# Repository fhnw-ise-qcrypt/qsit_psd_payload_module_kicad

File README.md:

# qsit_psd_payload_module_kicad
kicad drawings to interface a position sensitive detector (diode) for the QSIT payload

### BOM

https://octopart.com/bom-tool/2UpAKjyw

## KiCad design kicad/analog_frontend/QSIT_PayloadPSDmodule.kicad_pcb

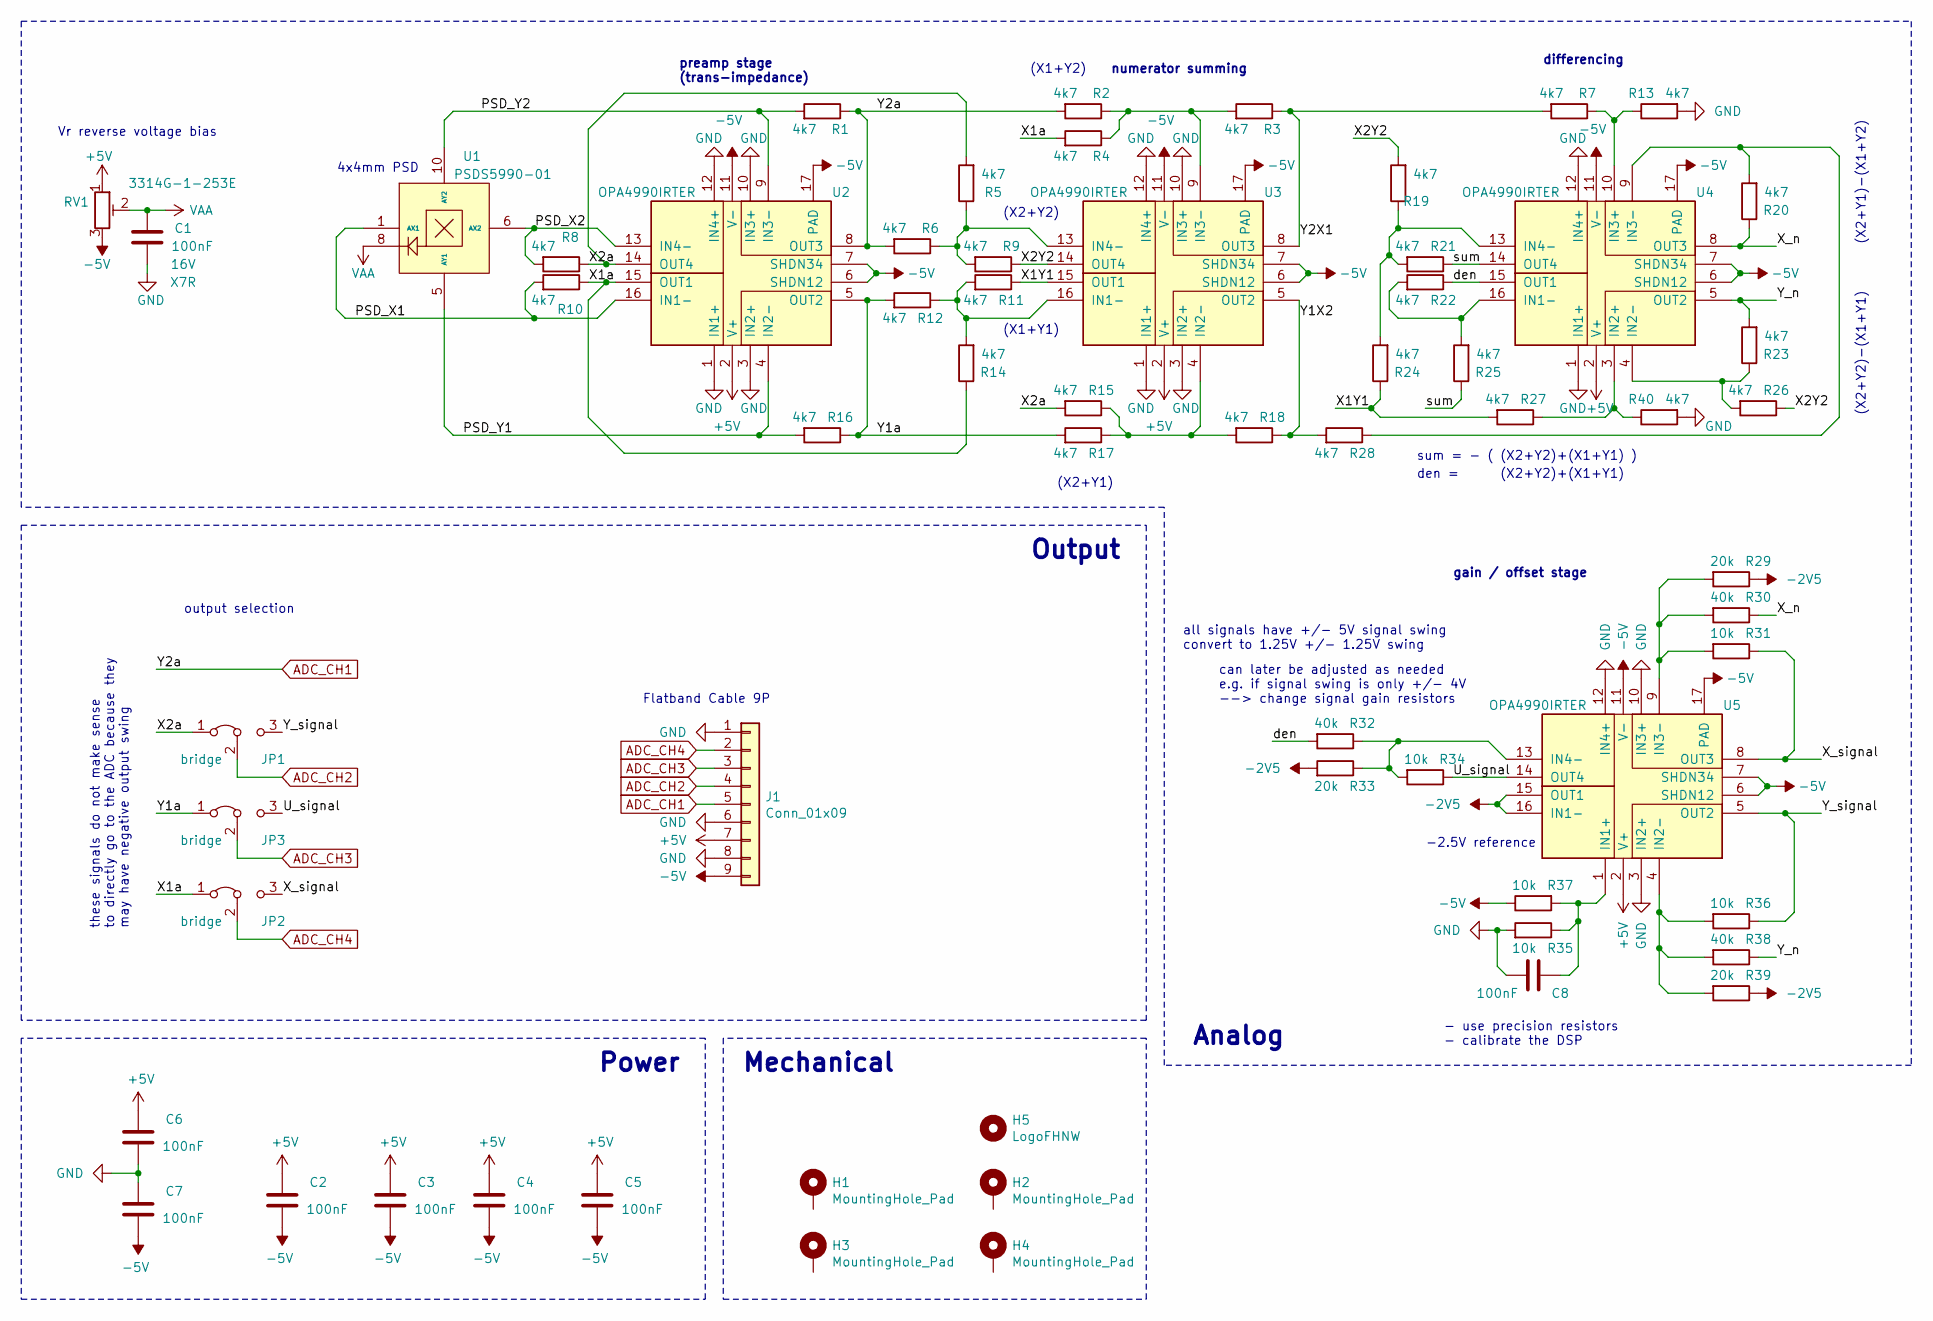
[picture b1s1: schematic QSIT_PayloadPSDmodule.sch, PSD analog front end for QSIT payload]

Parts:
C1: 100nF; C_0603_1608Metric_Pad1.08x0.95mm_HandSolder; Voltage 16V
C2, C3, C4, C5, C6, C7, C8: 100nF; C_0603_1608Metric_Pad1.08x0.95mm_HandSolder
H1, H2, H3, H4: MountingHole_Pad; MountingHole_2.5mm
H5: LogoFHNW; Logo_FHNW_03x05mm
J1: Conn_01x09; PinHeader_1x09_P2.54mm_Vertical
JP1, JP2, JP3: bridge; SolderJumper-3_P1.3mm_Open_RoundedPad1.0x1.5mm
R1, R2, R3, R4, R5, R6, R7, R8, R9, R10, R11, R12, R13, R14, R15, R16, R17, R18, R19, R20, R21, R22, R23, R24, R25, R26, R27, R28, R40: 4k7; R_0603_1608Metric_Pad0.98x0.95mm_HandSolder
R29, R33, R39: 20k; R_0603_1608Metric_Pad0.98x0.95mm_HandSolder
R30, R32, R38: 40k; R_0603_1608Metric_Pad0.98x0.95mm_HandSolder
R31, R34, R35, R36, R37: 10k; R_0603_1608Metric_Pad0.98x0.95mm_HandSolder
RV1: 3314G-1-253E; Potentiometer_Bourns_3314R-GM5_Vertical
U1: PSDS5990-01; HAMAMATSU_PSD_S599001_4mm
U2, U3, U4, U5: OPA4990IRTER; WQFN-16-1EP_3x3mm_P0.5mm_EP1.6x1.6mm

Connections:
+5V: C2.2, C3.2, C4.2, C5.2, C6.2, J1.7, RV1.1, U2.2 (V+), U3.2 (V+), U4.2 (V+), U5.2 (V+)
-2V5: R29.1, R33.2, R39.1, U5.15 (OUT1), U5.16 (IN1-)
-5V: C2.1, C3.1, C4.1, C5.1, C7.1, J1.9, R37.1, RV1.3, U2.6 (SHDN12), U2.7 (SHDN34), U2.11 (V-), U2.17 (PAD), U3.6 (SHDN12), U3.7 (SHDN34), U3.11 (V-), U3.17 (PAD), U4.6 (SHDN12), U4.7 (SHDN34), U4.11 (V-), U4.17 (PAD), U5.6 (SHDN12), U5.7 (SHDN34), U5.11 (V-), U5.17 (PAD)
/PSD_X1: R10.2, U1.1 (AX1), U2.16 (IN1-)
/PSD_X2: R8.2, U1.6 (AX2), U2.13 (IN4-)
/PSD_Y1: R16.2, U1.5 (AY1), U2.4 (‌IN2-)
/PSD_Y2: R1.2, U1.10 (AY2), U2.9 (IN3-)
/U_signal: JP3.3 (B), R34.1, U5.14 (OUT4)
/X1Y1: R11.1, R24.1, R27.2, U3.15 (OUT1)
/X1a: JP2.1 (A), R4.2, R10.1, R14.1, U2.15 (OUT1)
/X2Y2: R9.1, R19.2, R26.1, U3.14 (OUT4)
/X2a: JP1.1 (A), R5.2, R8.1, R15.2, U2.14 (OUT4)
/X_n: R20.1, R30.1, U4.8 (OUT3)
/X_signal: JP2.3 (B), R31.1, U5.8 (OUT3)
/Y1X2: R18.1, R28.2, U3.5 (OUT2)
/Y1a: JP3.1 (A), R12.2, R16.1, R17.2, U2.5 (OUT2)
/Y2X1: R3.1, R7.2, U3.8 (OUT3)
/Y_n: R23.2, R38.1, U4.5 (OUT2)
/Y_signal: JP1.3 (B), R36.1, U5.5 (OUT2)
/den: R22.1, R32.2, U4.15 (OUT1)
/sum: R21.1, R25.1, U4.14 (OUT4)
ADC_CH1: J1.5, R1.1, R2.2, R6.2, U2.8 (OUT3)
ADC_CH2: J1.4, JP1.2 (C)
ADC_CH3: J1.3, JP3.2 (C)
ADC_CH4: J1.2, JP2.2 (C)
GND: C1.1, C6.1, C7.2, C8.1, J1.1, J1.6, J1.8, R13.2, R35.2, R40.2, U2.1 (IN1+), U2.3 (IN2+), U2.10 (IN3+), U2.12 (IN4+), U3.1 (IN1+), U3.3 (IN2+), U3.10 (IN3+), U3.12 (IN4+), U4.1 (IN1+), U4.12 (IN4+), U5.3 (IN2+), U5.10 (IN3+), U5.12 (IN4+)
unnamed: C8.2, R35.1, R37.2, U5.1 (IN1+)
unnamed: R2.1, R3.2, R4.1, U3.9 (IN3-)
unnamed: R5.1, R6.1, R9.2, U3.13 (IN4-)
unnamed: R11.2, R12.1, R14.2, U3.16 (IN1-)
unnamed: R7.1, R13.1, U4.10 (IN3+)
unnamed: R15.1, R17.1, R18.2, U3.4 (‌IN2-)
unnamed: R19.1, R21.2, R24.2, U4.13 (IN4-)
unnamed: R20.2, R28.1, U4.9 (IN3-)
unnamed: R22.2, R25.2, U4.16 (IN1-)
unnamed: R23.1, R26.2, U4.4 (‌IN2-)
unnamed: R27.1, R40.1, U4.3 (IN2+)
unnamed: R29.2, R30.2, R31.2, U5.9 (IN3-)
unnamed: R32.1, R33.1, R34.2, U5.13 (IN4-)
unnamed: R36.2, R38.2, R39.2, U5.4 (‌IN2-)
VAA: C1.2, RV1.2, U1.8

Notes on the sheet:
Vr reverse voltage bias
4x4mm PSD
preamp stage (trans-impedance)
numerator summing
differencing
(X2+Y1)
(X1+Y2)
(X1+Y1)
(X2+Y2)
(X2+Y1)-(X1+Y2)
(X2+Y2)-(X1+Y1)
den = (X2+Y2)+(X1+Y1)
sum = - ( (X2+Y2)+(X1+Y1) )
gain / offset stage
all signals have +/- 5V signal swing convert to 1.25V +/- 1.25V swing
can later be adjusted as needed e.g. if signal swing is only +/- 4V --> change signal gain resistors
Flatband Cable 9P
Mechanical
-2.5V reference
Power
Output
Analog
output selection
these signals do not make sense to directly go to the ADC because they may have negative output swing
- use precision resistors - calibrate the DSP

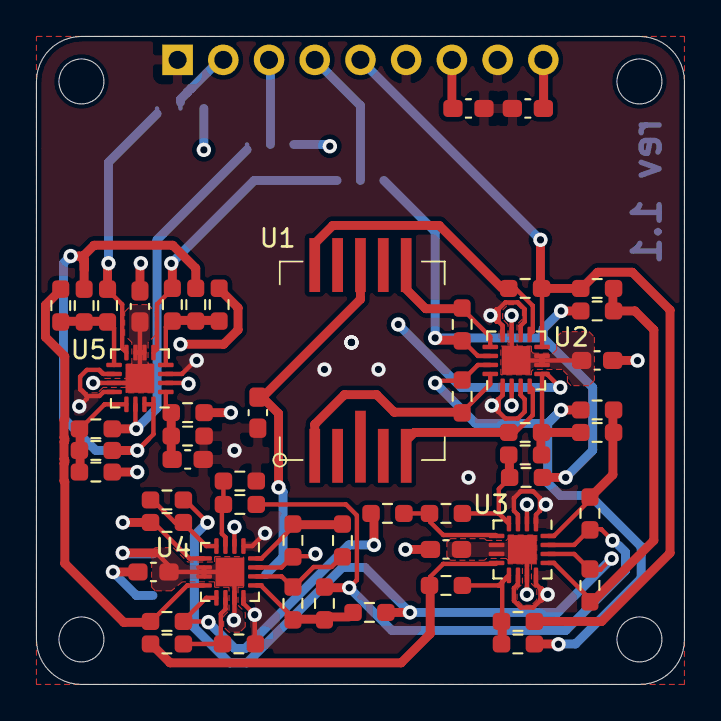
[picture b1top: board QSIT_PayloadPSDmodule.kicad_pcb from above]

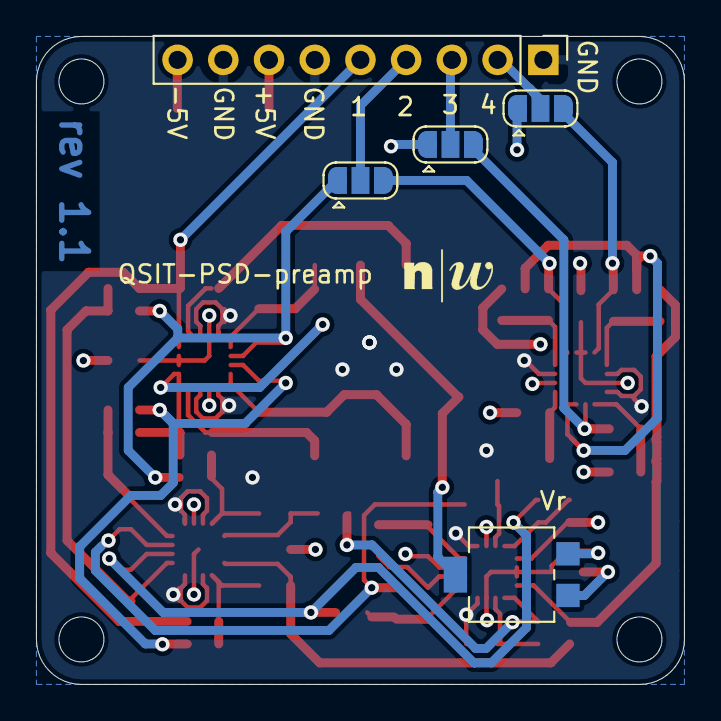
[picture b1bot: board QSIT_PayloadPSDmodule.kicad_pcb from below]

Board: 4 copper layers, 36.0 x 36.0 mm, 63 parts (6 on the bottom side), 41 nets.

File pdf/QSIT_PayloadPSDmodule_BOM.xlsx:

Reference | Quantity | Value | Footprint | Datasheet | Type | Voltage
C1 C2 C3 C4 C5 C6 C7 C8 | 8 | 100nF | Capacitor_SMD:C_0603_1608Metric_Pad1.08x0.95mm_HandSolder | ~ | X7R | 16V
H1 H2 H3 H4 | 4 | MountingHole_Pad | Mounting_Holes:MountingHole_2.5mm | ~
J1 | 1 | Conn_01x09 | Connector_PinHeader_2.54mm:PinHeader_1x09_P2.54mm_Vertical | ~
JP1 JP2 JP3 | 3 | bridge | Jumper:SolderJumper-3_P1.3mm_Open_RoundedPad1.0x1.5mm | ~
R1 R2 R3 R4 R5 R6 R7 R8 R9 R10 R11 R12 R13 R14 R15 R16 R17 R18 R19 R20 R21 R22 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 | 29 | 4k7 | Resistor_SMD:R_0603_1608Metric_Pad0.98x0.95mm_HandSolder | ~
R30 R32 R38 | 3 | 20k | Resistor_SMD:R_0603_1608Metric_Pad0.98x0.95mm_HandSolder | ~
R29 R31 R33 R34 R35 R36 R37 R39 | 8 | 10k | Resistor_SMD:R_0603_1608Metric_Pad0.98x0.95mm_HandSolder | ~
RV1 | 1 | 3314G-1-253E | Potentiometer_SMD:Potentiometer_Bourns_3314R-GM5_Vertical | ~
U1 | 1 | PSDS5990-01 | simonmartin_kicad_lib:HAMAMATSU_PSD_S599001_4mm
U2 U3 U4 U5 | 4 | OPA4990IRTER | Package_DFN_QFN:WQFN-16-1EP_3x3mm_P0.5mm_EP1.6x1.6mm

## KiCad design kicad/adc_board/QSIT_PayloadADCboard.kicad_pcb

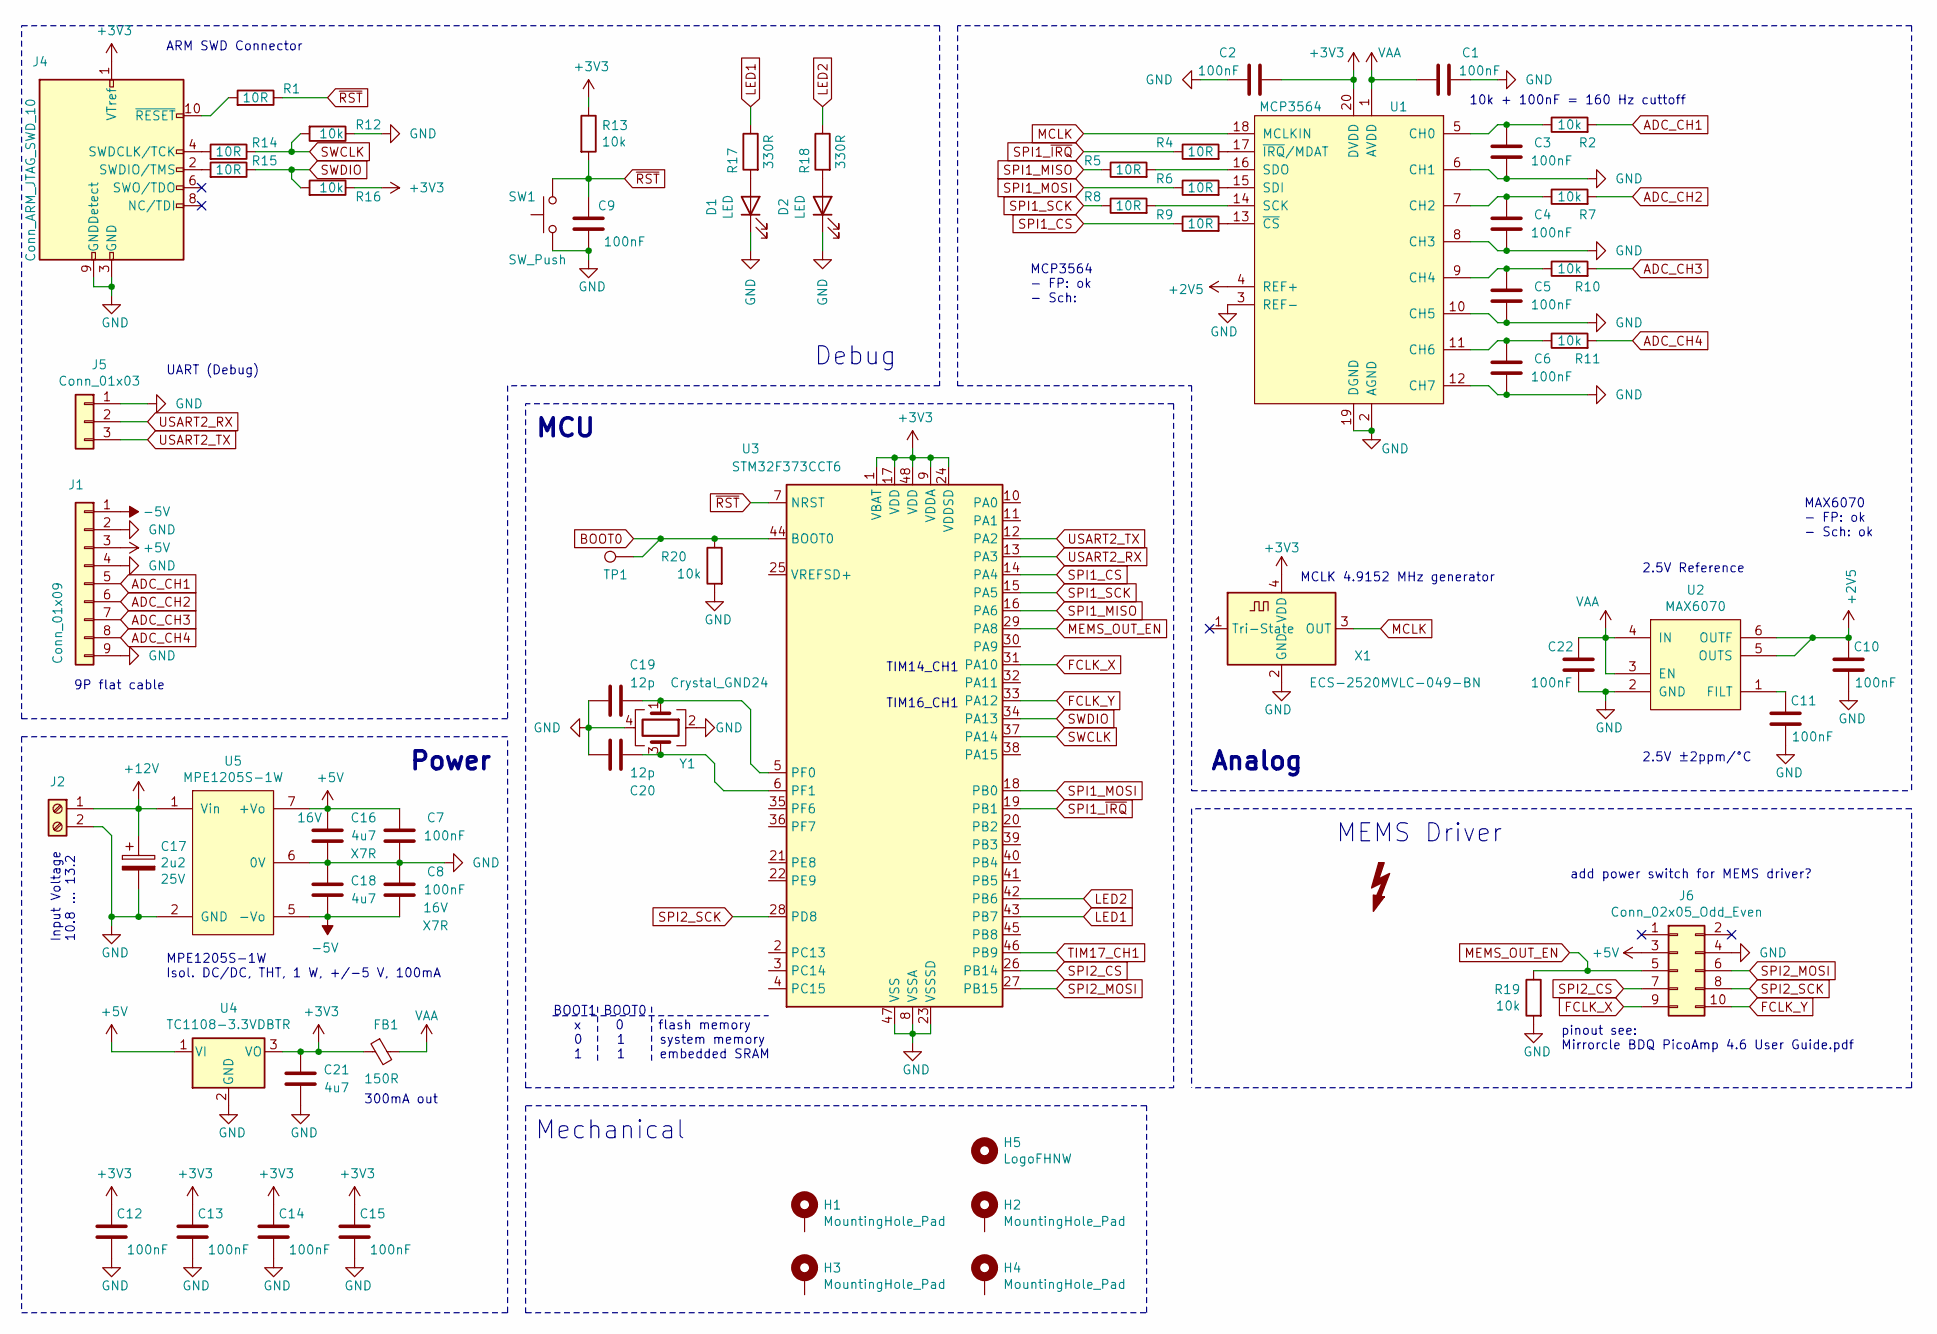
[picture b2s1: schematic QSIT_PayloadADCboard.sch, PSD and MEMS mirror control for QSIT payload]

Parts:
C1, C2, C3, C4, C5, C6, C7, C8, C9, C10, C11, C12, C13, C14, C15: 100nF; C_0603_1608Metric_Pad1.05x0.95mm_HandSolder; Voltage 16V
C16, C18, C21: 4u7; C_1206_3216Metric; Voltage 16V
C17: 2u2; CP_Radial_D4.0mm_P2.00mm; Voltage 25V
C19, C20: 12p; C_0603_1608Metric_Pad1.05x0.95mm_HandSolder; Voltage 16V
C22: 100nF; C_0603_1608Metric; Voltage 16V
D1, D2: LED; LED_0805_2012Metric_Pad1.15x1.40mm_HandSolder
FB1: 150R; R_0603_1608Metric_Pad1.05x0.95mm_HandSolder
H1, H2, H3, H4: MountingHole_Pad; MountingHole_2.5mm
H5: LogoFHNW; Logo_FHNW_03x05mm
J1: Conn_01x09; PinHeader_1x09_P2.54mm_Vertical
J2: Power_Conn; TerminalBlock_4Ucon_1x02_P3.50mm_Horizontal
J4: Conn_ARM_JTAG_SWD_10; PinHeader_2x05_P1.27mm_Vertical_SMD
J5: Conn_01x03; PinHeader_1x03_P2.54mm_Vertical
J6: Conn_02x05_Odd_Even; PinHeader_2x05_P1.27mm_Vertical_SMD
R1, R4, R5, R6, R8, R9, R14, R15: 10R; R_0603_1608Metric_Pad1.05x0.95mm_HandSolder
R2, R7, R10, R11, R12, R13, R16, R19, R20: 10k; R_0603_1608Metric_Pad1.05x0.95mm_HandSolder
R17, R18: 330R; R_0603_1608Metric_Pad1.05x0.95mm_HandSolder
SW1: SW_Push; SW_Push_1P1T_NO_CK_KMR2
TP1: TestPoint; TestPoint_Keystone_5000-5004_Miniature
U1: MCP3564; TSSOP-20_4.4x6.5mm_P0.65mm
U2: MAX6070; SOT-23-6_Handsoldering
U3: STM32F373CCT6; LQFP-48_7x7mm_P0.5mm
U4: TC1108-3.3VDBTR; SOT-223-3_TabPin2
U5: MPE1205S-1W; Converter_DCDC_multicorp_THT
X1: ECS-2520MVLC-049-BN; Oscillator_SMD_ECS_2520MV-xxx-xx-4Pin_2.5x2.0mm
Y1: Crystal_GND24; Crystal_SMD_TXC_7M-4Pin_3.2x2.5mm

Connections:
+2V5: C10.2, U1.4 (REF+), U2.5 (OUTS), U2.6 (OUTF)
+3V3: C2.1, C12.2, C13.2, C14.2, C15.2, C21.2, FB1.1, J4.1 (VTref), R13.1, R16.1, U1.20 (DVDD), U3.1 (VBAT), U3.9 (VDDA), U3.17 (VDD), U3.24 (VDDSD), U3.48 (VDD), U4.3 (VO), X1.4 (VDD)
+5V: C7.2, C16.2, J1.3, J6.3, U4.1 (VI), U5.7 (+Vo)
+12V: C17.1, J2.1, U5.1 (Vin)
-5V: C8.1, C18.1, J1.1, U5.5 (-Vo)
ADC_CH1: J1.5, R2.2
ADC_CH2: J1.6, R7.2
ADC_CH3: J1.7, R10.2
ADC_CH4: J1.8, R11.2
BOOT0: R20.1, TP1.1, U3.44 (BOOT0)
FCLK_X: J6.9, U3.31 (PA10)
FCLK_Y: J6.10, U3.33 (PA12)
GND: C1.2, C2.2, C3.1, C4.1, C5.1, C6.1, C7.1, C8.2, C9.1, C10.1, C11.1, C12.1, C13.1, C14.1, C15.1, C16.1, C17.2, C18.2, C19.2, C20.2, C21.1, C22.1, D1.1 (K), D2.1 (K), J1.2, J1.4, J1.9, J2.2, J4.3 (GND), J4.5 (GND), J4.9 (GNDDetect), J5.1, J6.4, R12.1, R19.2, R20.2, SW1.1, U1.2 (AGND), U1.3 (REF-), U1.6 (CH1), U1.8 (CH3), U1.10 (CH5), U1.12 (CH7), U1.19 (DGND), U2.2 (GND), U3.8 (VSSA), U3.23 (VSSSD), U3.47 (VSS), U4.2 (GND), U5.2 (GND), U5.6 (0V), X1.2 (GND), Y1.2, Y1.4
LED1: R17.1, U3.43 (PB7)
LED2: R18.1, U3.42 (PB6)
MCLK: U1.18 (MCLKIN), X1.3 (OUT)
MEMS_OUT_EN: J6.5, R19.1, U3.29 (PA8)
unnamed: C3.2, R2.1, U1.5 (CH0)
unnamed: C4.2, R7.1, U1.7 (CH2)
unnamed: C5.2, R10.1, U1.9 (CH4)
unnamed: C6.2, R11.1, U1.11 (CH6)
unnamed: C11.2, U2.1 (FILT)
unnamed: C19.1, U3.5 (PF0), Y1.1
unnamed: C20.1, U3.6 (PF1), Y1.3
unnamed: D1.2 (A), R17.2
unnamed: D2.2 (A), R18.2
unnamed: J4.2 (SWDIO/TMS), R15.2
unnamed: J4.4 (SWDCLK/TCK), R14.2
unnamed: J4.10 (~RESET~), R1.2
unnamed: R4.2, U1.17 (~IRQ~/MDAT)
unnamed: R5.2, U1.16 (SDO)
unnamed: R6.2, U1.15 (SDI)
unnamed: R8.2, U1.14 (SCK)
unnamed: R9.2, U1.13 (~CS~)
SPI1_CS: R9.1, U3.14 (PA4)
SPI1_MISO: R5.1, U3.16 (PA6)
SPI1_MOSI: R6.1, U3.18 (PB0)
SPI1_SCK: R8.1, U3.15 (PA5)
SPI1_~IRQ~: R4.1, U3.19 (PB1)
SPI2_CS: J6.7, U3.26 (PB14)
SPI2_MOSI: J6.6, U3.27 (PB15)
SPI2_SCK: J6.8, U3.28 (PD8)
SWCLK: R12.2, R14.1, U3.37 (PA14)
SWDIO: R15.1, R16.2, U3.34 (PA13)
TIM17_CH1: U3.46 (PB9)
USART2_RX: J5.2, U3.13 (PA3)
USART2_TX: J5.3, U3.12 (PA2)
VAA: C1.1, C22.2, FB1.2, U1.1 (AVDD), U2.3 (EN), U2.4 (IN)
~RST: C9.2, R1.1, R13.2, SW1.2, U3.7 (NRST)

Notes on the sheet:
10k + 100nF = 160 Hz cuttoff
pinout see: Mirrorcle BDQ PicoAmp 4.6 User Guide.pdf
add power switch for MEMS driver?
MPE1205S-1W Isol. DC/DC, THT, 1 W, +/-5 V, 100mA
300mA out
2.5V ±2ppm/°C
Input Voltage 10.8 ... 13.2
ARM SWD Connector
UART (Debug)
2.5V Reference
9P flat cable
MCLK 4.9152 MHz generator
Power
MCU
Debug
Analog
MEMS Driver
Mechanical
BOOT1 BOOT0 x 0 flash memory 0 1 system memory 1 1 embedded SRAM
MAX6070 - FP: ok - Sch: ok
MCP3564 - FP: ok - Sch:
TIM14_CH1
TIM16_CH1

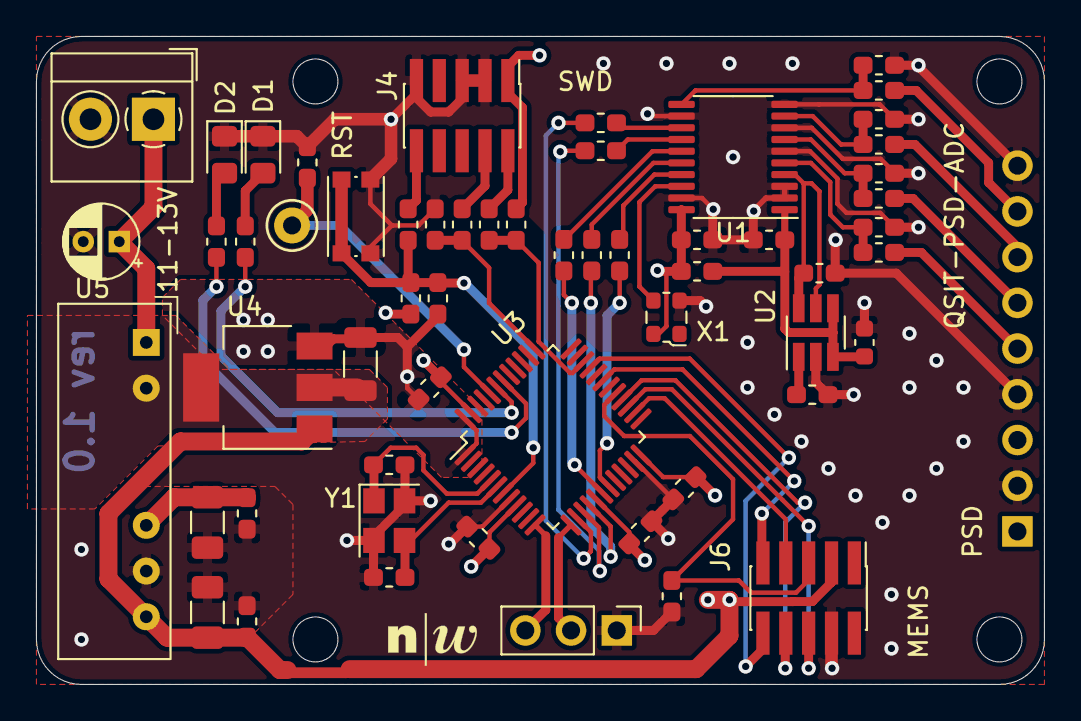
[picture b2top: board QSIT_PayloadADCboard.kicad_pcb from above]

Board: 4 copper layers, 56.0 x 36.0 mm, 63 parts (1 on the bottom side), 48 nets.

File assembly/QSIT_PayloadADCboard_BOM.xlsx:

Reference | Quantity | Value | Footprint | Datasheet | Type | Voltage
C16 C18 C21 | 3 | 4u7 | Capacitor_SMD:C_1206_3216Metric | ~ | X7R | 16V
C17 | 1 | 2u2 | Capacitor_THT:CP_Radial_D4.0mm_P2.00mm | ~ |  | 25V
C19 C20 | 2 | 12p | Capacitor_SMD:C_0603_1608Metric_Pad1.05x0.95mm_HandSolder | ~ | X7R | 16V
C22 | 1 | 100nF | Capacitor_SMD:C_0603_1608Metric | ~ | X7R | 16V
C1 C2 C3 C4 C5 C6 C7 C8 C9 C10 C11 C12 C13 C14 C15 | 15 | 100nF | Capacitor_SMD:C_0603_1608Metric_Pad1.05x0.95mm_HandSolder | ~ | X7R | 16V
D1 D2 | 2 | LED | LED_SMD:LED_0805_2012Metric_Pad1.15x1.40mm_HandSolder | ~
FB1 | 1 | 150R | Resistor_SMD:R_0603_1608Metric_Pad1.05x0.95mm_HandSolder | ~
J1 | 1 | Conn_01x09 | Connector_PinHeader_2.54mm:PinHeader_1x09_P2.54mm_Vertical | ~
J2 | 1 | Power_Conn | TerminalBlock_4Ucon:TerminalBlock_4Ucon_1x02_P3.50mm_Horizontal | ~
J4 | 1 | Conn_ARM_JTAG_SWD_10 | Connector_PinHeader_1.27mm:PinHeader_2x05_P1.27mm_Vertical_SMD
J5 | 1 | Conn_01x03 | Connector_PinHeader_2.54mm:PinHeader_1x03_P2.54mm_Vertical | ~
J6 | 1 | Conn_02x05_Odd_Even | Connector_PinHeader_1.27mm:PinHeader_2x05_P1.27mm_Vertical_SMD | ~
R17 R18 | 2 | 330R | Resistor_SMD:R_0603_1608Metric_Pad1.05x0.95mm_HandSolder | ~
R2 R7 R10 R11 R12 R13 R16 R19 R20 | 9 | 10k | Resistor_SMD:R_0603_1608Metric_Pad1.05x0.95mm_HandSolder | ~
R1 R4 R5 R6 R8 R9 R14 R15 | 8 | 10R | Resistor_SMD:R_0603_1608Metric_Pad1.05x0.95mm_HandSolder | ~
SW1 | 1 | SW_Push | Button_Switch_SMD:SW_Push_1P1T_NO_CK_KMR2 | ~
U1 | 1 | MCP3564 | Package_SO:TSSOP-20_4.4x6.5mm_P0.65mm
U2 | 1 | MAX6070 | Package_TO_SOT_SMD:SOT-23-6_Handsoldering
U3 | 1 | STM32F373CCT6 | Package_QFP:LQFP-48_7x7mm_P0.5mm
U4 | 1 | TC1108-3.3VDBTR | Package_TO_SOT_SMD:SOT-223-3_TabPin2
U5 | 1 | MPE1205S-1W | simonmartin_kicad_lib:Converter_DCDC_multicorp_THT
X1 | 1 | ECS-2520MVLC-049-BN | Oscillator:Oscillator_SMD_ECS_2520MV-xxx-xx-4Pin_2.5x2.0mm
Y1 | 1 | Crystal_GND24 | Crystal:Crystal_SMD_TXC_7M-4Pin_3.2x2.5mm | ~

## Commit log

2021-11-24 initial analog opamp version
2021-11-29 new ADC board
2021-12-03 changed to single 9pin connector
2021-12-03 added stm32f373cct6
2021-12-06 STM32 board ready for review
2021-12-10 further pcb improvements
2021-12-10 rev.1 of ADC board
2021-12-20 ignore gerber
2021-12-20 ignore ltspice
2021-12-20 rev 1 finished - final check on PSD frontend - plotted gerbber for jlc - added simulation for PSD frontend
2022-02-07 added assembly documentation
2022-07-25 SWDIO/SWCLK swapped
2022-08-17 fixed wrong connection to PSD X/Y axis
